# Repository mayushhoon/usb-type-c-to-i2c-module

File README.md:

# USB Type-C to I2C Bridge Module using FT201X IC

## Overview
A highly compact, production-ready USB Type-C to I2C hardware bridge. This module is designed to interface high-speed USB data from a host PC directly with external I2C peripherals, displays, and sensors. 

Engineered with a strict focus on Design for Manufacturability (DFM) and Design for Assembly (DFA), the board packs power regulation, signal filtering, and data conversion into a 31x17mm footprint using high-density 0603 surface-mount components.

| Front Side | Back Side |
| :---: | :---: |
|  |  |

## Hardware Architecture
* **Core Bridge IC:** FTDI FT201X (Full-Speed USB to I2C Bridge).
* **Power Regulation:** Integrated 3.3V Low Dropout (LDO) regulator to provide clean, low-noise power to both the internal logic and external I2C header.
* **EMI Suppression:** Custom RC low-pass filter network (27Ω / 47pF) on the USB D+ and D- data lines for impedance matching and high-frequency noise mitigation.
* **Bus Stability:** Dedicated 2.2kΩ hardware pull-up resistors on the SDA and SCL lines to guarantee sharp signal edge-rates at Fast Mode (400 kHz) clock speeds.
* **Host Isolation:** Ferrite bead input filtering on the 5V VBUS to block high-frequency switching noise from the host PC.

## Diagnostic Interface
The module features a custom diagnostic LED array utilizing the configurable CBUS pins of the FT201X to provide immediate visual feedback of bus states:
* 🔴 **RED:** Power indicator (Tapped downstream of the input filter).
* 🔵 **BLUE:** RX Data Activity.
* 🟢 **GREEN:** TX Data Activity.

## Board Specifications
| Feature | Specification |
| :--- | :--- |
| **Dimensions** | 31mm x 17mm |
| **Layers** | 2-Layer FR4 (Solid bottom ground plane) |
| **Component Size** | 0603 Imperial (Passives & LEDs) |
| **Trace Width** | 0.254mm (10 mil) standard |
| **Input Interface** | USB Type-C (Receptacle) |
| **Output Interface** | 4-Pin 2.54mm Header (3V3, GND, SCL, SDA) |

## Repository Structure
* `/Hardware` - Source KiCad 7/8 project files (Schematic and PCB layout).
* `/Fabrication` - Manufacturing package (Gerbers, Excellon Drill files, and CSV BOM).
* `/Docs` - PDF schematics, 3D renders, and component datasheets.

## Assembly Notes
This board was intentionally designed to be hand-solderable despite its small size. All passive components use the `_HandSoldering` 0603 footprint variants to provide extended pad surface area for tweezer and iron assembly. Ensure the FT201X internal CBUS pins are configured via the FT_Prog utility to activate the TX and RX LED indicators after assembly.

## Author
**Designed by MAYUSH RAHANGDALE**

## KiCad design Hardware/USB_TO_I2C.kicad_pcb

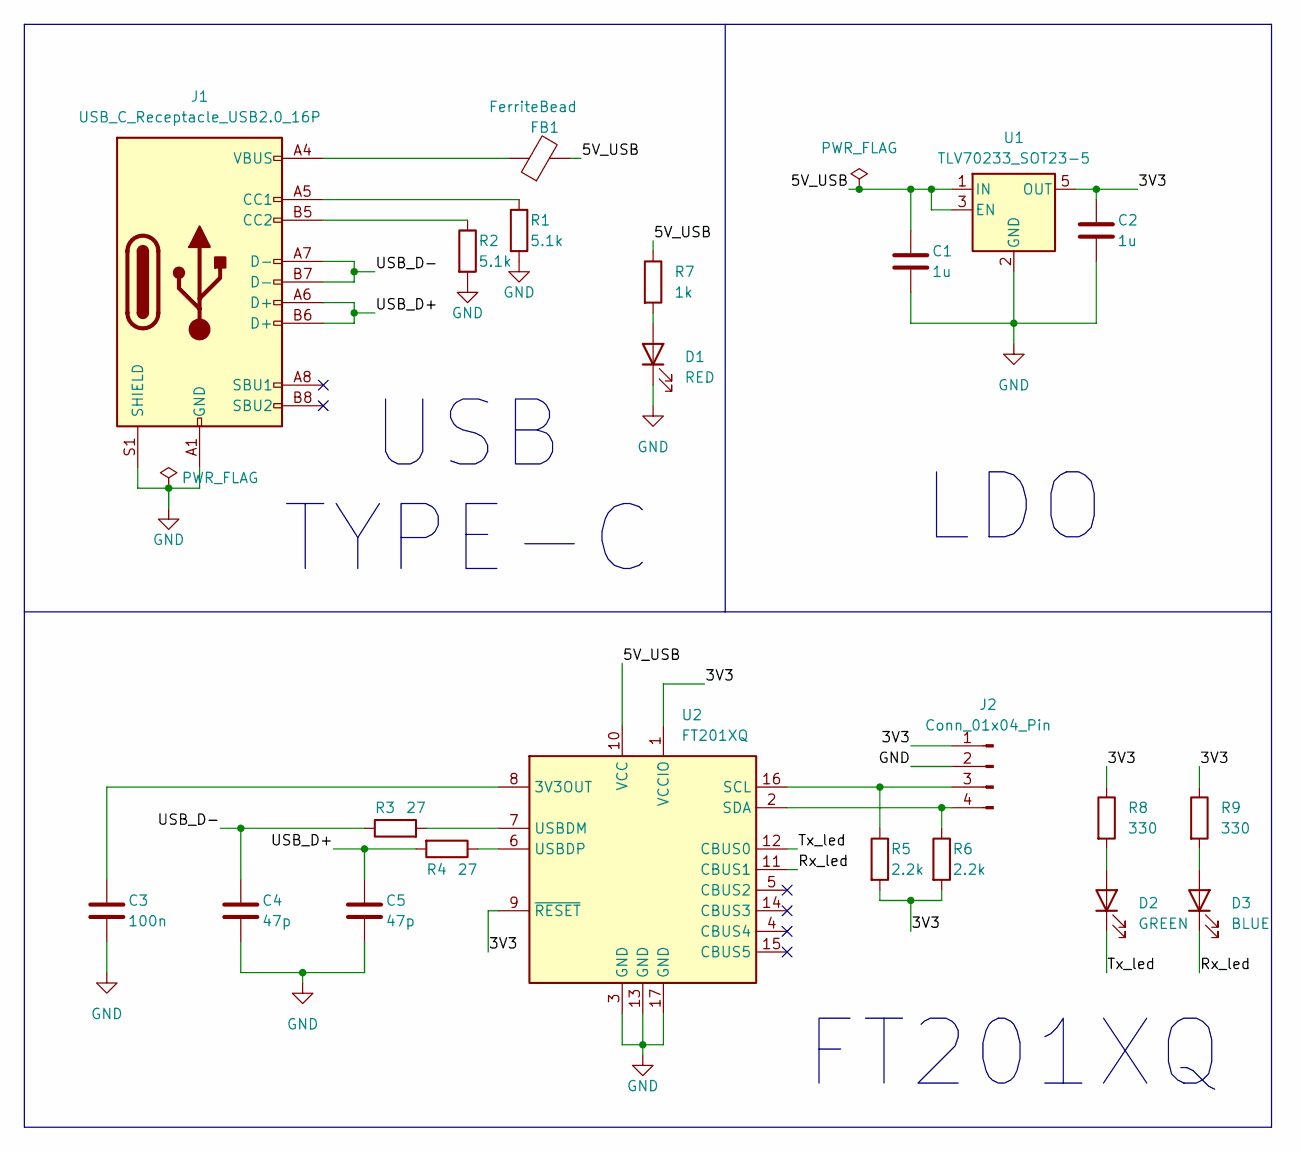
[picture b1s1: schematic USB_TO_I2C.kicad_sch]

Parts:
C1, C2: 1u; C_0603_1608Metric_Pad1.08x0.95mm_HandSolder
C3: 100n; C_0603_1608Metric_Pad1.08x0.95mm_HandSolder
C4, C5: 47p; C_0603_1608Metric_Pad1.08x0.95mm_HandSolder
D1: RED; LED_0603_1608Metric_Pad1.05x0.95mm_HandSolder
D2: GREEN; LED_0603_1608Metric_Pad1.05x0.95mm_HandSolder
D3: BLUE; LED_0603_1608Metric_Pad1.05x0.95mm_HandSolder
FB1: FerriteBead; L_0603_1608Metric_Pad1.05x0.95mm_HandSolder
J1: USB_C_Receptacle_USB2.0_16P; USB_C_Receptacle_HRO_TYPE-C-31-M-12
J2: Conn_01x04_Pin; PinHeader_1x04_P2.54mm_Vertical
R1, R2: 5.1k; R_0603_1608Metric_Pad0.98x0.95mm_HandSolder
R3, R4: 27; R_0603_1608Metric_Pad0.98x0.95mm_HandSolder
R5, R6: 2.2k; R_0603_1608Metric_Pad0.98x0.95mm_HandSolder
R7: 1k; R_0603_1608Metric_Pad0.98x0.95mm_HandSolder
R8, R9: 330; R_0603_1608Metric_Pad0.98x0.95mm_HandSolder
U1: TLV70233_SOT23-5; SOT-23-5
U2: FT201XQ; QFN-16-1EP_4x4mm_P0.65mm_EP2.1x2.1mm

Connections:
/3V3: C2.1, J2.1, R5.2, R6.2, R8.1, R9.1, U1.5 (OUT), U2.1 (VCCIO), U2.9 (~RESET)
/5V_USB: C1.1, FB1.2, R7.1, U1.1 (IN), U1.3 (EN), U2.10 (VCC)
/Rx_led: D3.1 (K), U2.11 (CBUS1)
/Tx_led: D2.1 (K), U2.12 (CBUS0)
/USB_D+: C5.1, J1.A6 (D+), J1.B6 (D+), R4.2
/USB_D-: C4.1, J1.A7 (D-), J1.B7 (D-), R3.1
GND: C1.2, C2.2, C3.2, C4.2, C5.2, D1.1 (K), J1.A1 (GND), J1.A12 (GND), J1.B1 (GND), J1.B12 (GND), J1.S1 (SHIELD), J2.2, R1.2, R2.2, U1.2 (GND), U2.3 (GND), U2.13 (GND), U2.17 (GND)
unnamed: D1.2 (A), R7.2
unnamed: D2.2 (A), R8.2
unnamed: D3.2 (A), R9.2
unnamed: FB1.1, J1.A4 (VBUS), J1.A9 (VBUS), J1.B4 (VBUS), J1.B9 (VBUS)
unnamed: J1.A5 (CC1), R1.1
unnamed: J1.B5 (CC2), R2.1
unnamed: J2.3, R5.1, U2.16 (SCL)
unnamed: J2.4, R6.1, U2.2 (SDA)
unnamed: C3.1, U2.8 (3V3OUT)
unnamed: R3.2, U2.7 (USBDM)
unnamed: R4.1, U2.6 (USBDP)

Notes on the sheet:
FT201XQ
USB TYPE-C
LDO

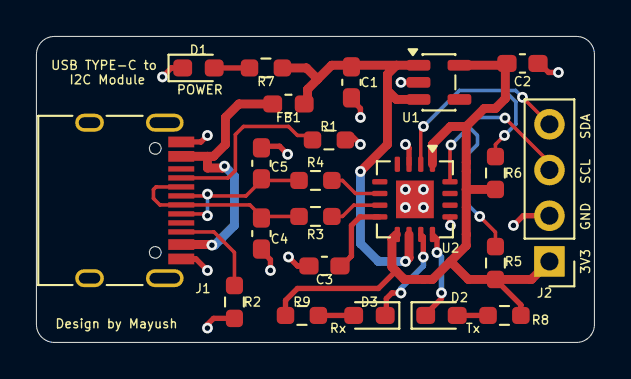
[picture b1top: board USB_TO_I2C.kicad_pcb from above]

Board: 2 copper layers, 31.0 x 17.0 mm, 22 parts (0 on the bottom side), 18 nets.
